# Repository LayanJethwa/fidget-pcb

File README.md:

# fidget-pcb

This is a fidget toy PCB that I made in Kicad. The layout currently is rectangular, but if you change the arrangement and print on 6 different PCBs, it should be possible to create a fidget cube.
Slack username: Layan Jethwa

There are 6 different modules, each of which has a different function:
- 6 different LEDs turn on if you press a button
- The buzzer activates if you press a button
- Two potentiometers, one of which controls the intensity of the LEDs and the other one the intensity of the buzzer
- A photo resistor that sounds the buzzer when blocked
- Two buttons, which when pressed at the same time, activate the LEDs
- Four buttons that are there for the clicky sound

## Schematic

## PCB

## BOM

- 1x battery cell holder
- 6x LED
- 1x flat motor
- 9x NPN transistor
- 1x photo resistor
- 20x resistor
- 2x potentiometer
- 8x button

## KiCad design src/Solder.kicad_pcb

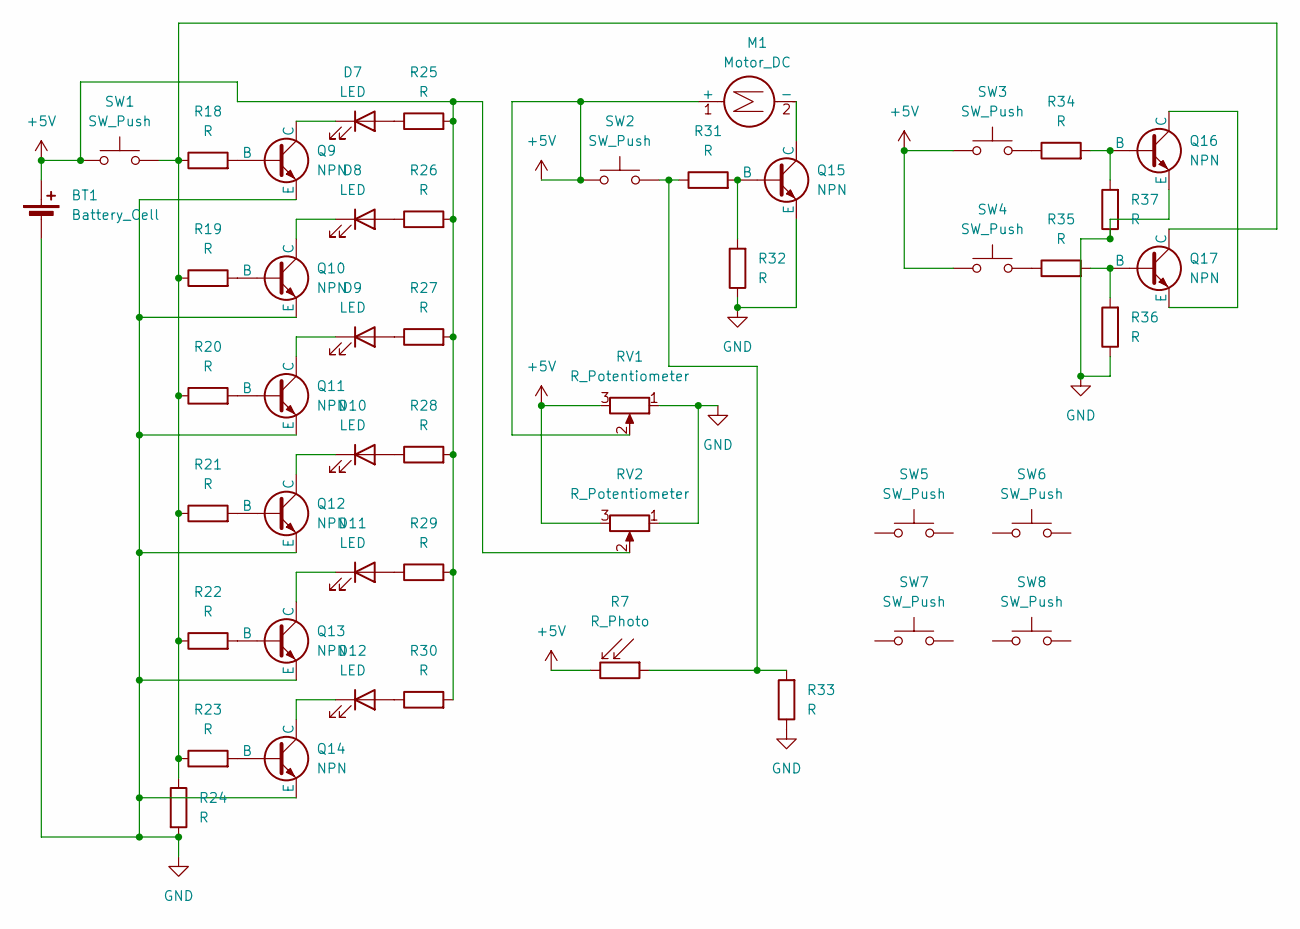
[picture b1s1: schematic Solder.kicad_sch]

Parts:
BT1: Battery_Cell; BatteryHolder_Keystone_3034_1x20mm
D7, D8, D9, D10, D11, D12: LED; LED_D5.0mm
M1: Motor_DC; PinHeader_1x02_P2.54mm_Vertical
Q9, Q10, Q11, Q12, Q13, Q14, Q15, Q16, Q17: NPN; TO-92L_HandSolder
R7: R_Photo; R_LDR_5.1x4.3mm_P3.4mm_Vertical
R18, R19, R20, R21, R22, R23, R24, R25, R26, R27, R28, R29, R30, R31, R32, R33, R34, R35, R36, R37: R; R_Axial_DIN0207_L6.3mm_D2.5mm_P7.62mm_Horizontal
RV1, RV2: R_Potentiometer; Potentiometer_Vishay_T73YP_Vertical
SW1, SW2, SW3, SW4, SW5, SW6, SW7, SW8: SW_Push; SW_PUSH_6mm

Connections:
+5V: BT1.1 (+), M1.1 (+), R7.2, R25.2, R26.2, R27.2, R28.2, R29.2, R30.2, RV1.2, RV1.3, RV2.2, RV2.3, SW1.1, SW2.1, SW3.1, SW4.1
GND: BT1.2 (-), Q9.3 (E), Q10.3 (E), Q11.3 (E), Q12.3 (E), Q13.3 (E), Q14.3 (E), Q15.3 (E), Q16.3 (E), R24.2, R32.1, R33.1, R36.1, R37.1, RV1.1, RV2.1
unnamed: D7.2 (A), R25.1
unnamed: D7.1 (K), Q9.1 (C)
unnamed: D8.2 (A), R26.1
unnamed: D8.1 (K), Q10.1 (C)
unnamed: D9.2 (A), R27.1
unnamed: D9.1 (K), Q11.1 (C)
unnamed: D10.2 (A), R28.1
unnamed: D10.1 (K), Q12.1 (C)
unnamed: D11.2 (A), R29.1
unnamed: D11.1 (K), Q13.1 (C)
unnamed: D12.2 (A), R30.1
unnamed: D12.1 (K), Q14.1 (C)
unnamed: M1.2 (-), Q15.1 (C)
unnamed: Q9.2 (B), R18.2
unnamed: Q10.2 (B), R19.2
unnamed: Q11.2 (B), R20.2
unnamed: Q12.2 (B), R21.2
unnamed: Q13.2 (B), R22.2
unnamed: Q14.2 (B), R23.2
unnamed: Q15.2 (B), R31.2, R32.2
unnamed: Q16.2 (B), R34.2, R37.2
unnamed: Q16.1 (C), Q17.3 (E)
unnamed: Q17.2 (B), R35.2, R36.2
unnamed: Q17.1 (C), R18.1, R19.1, R20.1, R21.1, R22.1, R23.1, R24.1, SW1.2
unnamed: R7.1, R31.1, R33.2, SW2.2
unnamed: R34.1, SW3.2
unnamed: R35.1, SW4.2

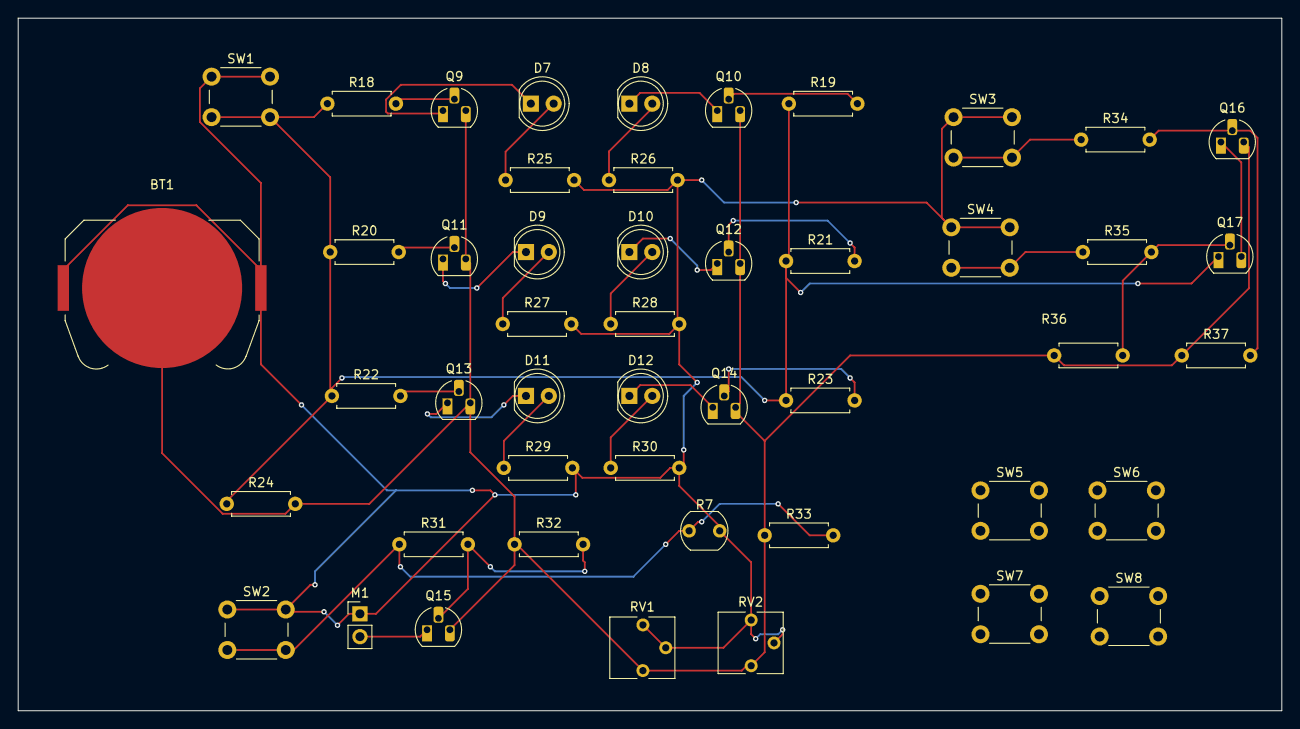
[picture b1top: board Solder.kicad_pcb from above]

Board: 2 copper layers, 140.5 x 77.0 mm, 48 parts (0 on the bottom side), 29 nets.

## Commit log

2025-07-02 Rename Screenshot 2025-07-02 050546.png to images/schematic.png
2025-07-02 Rename Screenshot 2025-07-02 050556.png to images/pcb.png
2025-07-02 Rename Screenshot 2025-07-02 050605.png to images/3d-model.png
2025-07-22 Rename Screenshot 2025-07-22 104701.png to pcb.png
2025-07-22 Rename Screenshot 2025-07-22 105306.png to 3d-model.png
2025-07-22 Rename Screenshot 2025-07-22 104701.png to pcb-image.png
2025-07-22 Rename Screenshot 2025-07-22 105306.png to model.png
